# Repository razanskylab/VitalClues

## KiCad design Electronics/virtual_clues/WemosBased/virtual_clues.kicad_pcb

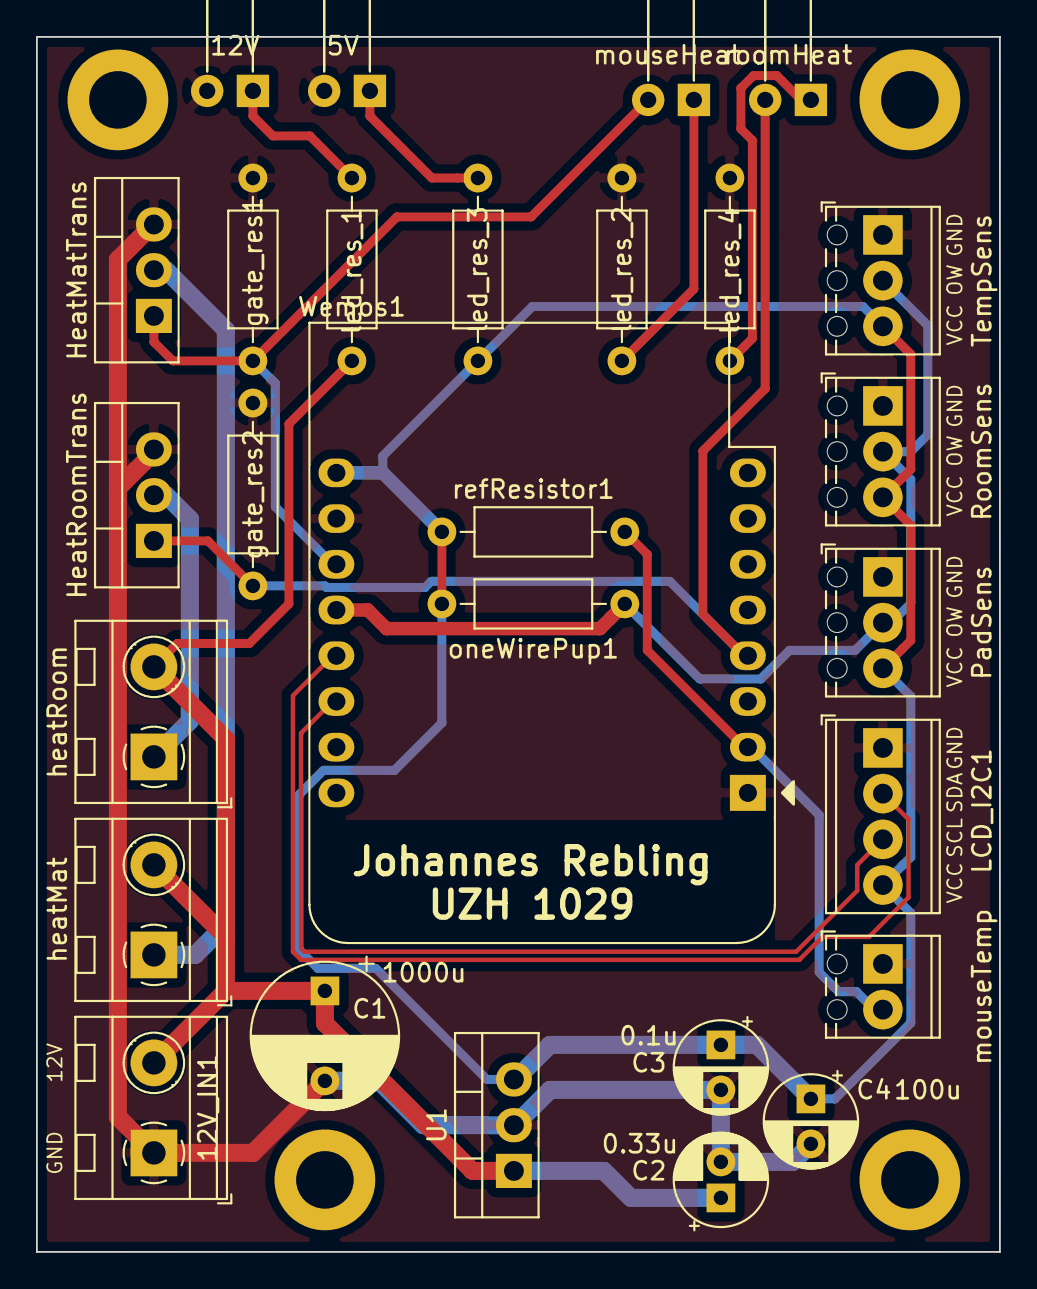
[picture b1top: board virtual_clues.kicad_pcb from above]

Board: 2 copper layers, 53.5 x 67.5 mm, 28 parts (0 on the bottom side), 15 nets.

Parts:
5V: red; LED_D5.0mm_Horizontal_O6.35mm_Z3.0mm
12V: green; LED_D5.0mm_Horizontal_O6.35mm_Z3.0mm
12V_IN1: 12V_IN; TerminalBlock_MetzConnect_Type094_RT03502HBLU_1x02_P5.00mm_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
C1: 1000u; CP_Radial_D8.0mm_P5.00mm
C2: 0.33u; CP_Radial_D5.0mm_P2.00mm
C3: 0.1u; CP_Radial_D5.0mm_P2.50mm
C4: 100u; CP_Radial_D5.0mm_P2.50mm
HeatMatTrans: IRLB8721PBF; TO-220-3_Vertical
HeatRoomTrans: IRLB8721PBF; TO-220-3_Vertical
LCD_I2C1: LCD_I2C; TerminalBlock_Phoenix_MPT-0,5-4-2.54_1x04_P2.54mm_Horizontal
PadSens: DigiTempSens1; TerminalBlock_Phoenix_MPT-0,5-3-2.54_1x03_P2.54mm_Horizontal
RoomSens: DigiTempSens2; TerminalBlock_Phoenix_MPT-0,5-3-2.54_1x03_P2.54mm_Horizontal
TempSens: DigiTempSens2; TerminalBlock_Phoenix_MPT-0,5-3-2.54_1x03_P2.54mm_Horizontal
U1: L7805; TO-220-3_Vertical
Wemos1: WeMos_D1_mini; WEMOS_D1_mini_light
gate_res1, gate_res2: 10k; R_Axial_DIN0207_L6.3mm_D2.5mm_P10.16mm_Horizontal
heatMat: heatMat1; TerminalBlock_MetzConnect_Type094_RT03502HBLU_1x02_P5.00mm_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
heatRoom: heatMat1; TerminalBlock_MetzConnect_Type094_RT03502HBLU_1x02_P5.00mm_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
led_res_1: 560; R_Axial_DIN0207_L6.3mm_D2.5mm_P10.16mm_Horizontal
led_res_2, led_res_3, led_res_4: 150; R_Axial_DIN0207_L6.3mm_D2.5mm_P10.16mm_Horizontal
mouseHeat: heaterLed; LED_D5.0mm_Horizontal_O6.35mm_Z3.0mm
mouseTemp: mouseTemp; TerminalBlock_Phoenix_MPT-0,5-2-2.54_1x02_P2.54mm_Horizontal
oneWirePup1: 4.7k; R_Axial_DIN0207_L6.3mm_D2.5mm_P10.16mm_Horizontal
refResistor1: 10k; R_Axial_DIN0207_L6.3mm_D2.5mm_P10.16mm_Horizontal
roomHeat: heaterLed; LED_D5.0mm_Horizontal_O6.35mm_Z3.0mm

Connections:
+12V: 12V_IN1.2, C1.1, C2.1, U1.1, heatMat.2, heatRoom.2, led_res_1.1
AnTempSens: Wemos1.2, mouseTemp.2, refResistor1.2
GND: 5V.2, 12V.2, 12V_IN1.1, C1.2, C2.2, C3.2, C4.2, HeatMatTrans.3, HeatRoomTrans.3, LCD_I2C1.1, PadSens.1, RoomSens.1, TempSens.1, U1.2, Wemos1.1, Wemos1.10, gate_res1.2, gate_res2.2, led_res_2.2, led_res_4.2, mouseTemp.1
HeatPadCtr: HeatMatTrans.1, Wemos1.11, gate_res1.1, mouseHeat.2
HeatRoom: HeatRoomTrans.1, Wemos1.4, gate_res2.1, roomHeat.2
unnamed: 5V.1, led_res_3.2
unnamed: 12V.1, led_res_1.2
unnamed: HeatMatTrans.2, heatMat.1
unnamed: HeatRoomTrans.2, heatRoom.1
unnamed: led_res_2.1, mouseHeat.1
unnamed: led_res_4.1, roomHeat.1
OneWireBus: PadSens.2, RoomSens.2, TempSens.2, Wemos1.12, oneWirePup1.2
SCL: LCD_I2C1.3, Wemos1.14
SDA: LCD_I2C1.2, Wemos1.13
VCC: C3.1, C4.1, LCD_I2C1.4, PadSens.3, RoomSens.3, TempSens.3, U1.3, Wemos1.9, led_res_3.1, oneWirePup1.1, refResistor1.1

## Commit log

2019-09-04 rough temperature monitoring
2019-09-05 pcb and first simple firmware added
2019-09-07 minor changes to nano firmware
2019-09-07 wemos working
2019-09-13 thingboard_testing
2019-09-14 ordered PCB & complete class based re-write
2019-09-15 update PCB for 3rd temp sensor and additional heat pad + better labels
2019-09-15 fancy self pointer
2019-09-26 new board soldered, all class based, now switching to adaio
2019-09-26 basic AIO working
2019-09-27 adding room and ambient feeds for AIO
2019-09-29 clean up + fixing 3.3V bug for temp sensing
2019-09-29 adding gitignore
2019-12-04 latest changes
2020-07-21 getting it to compile again, changing to small OLED display
